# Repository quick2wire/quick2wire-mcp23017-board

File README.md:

MCP23017 Port Extender Board
============================

This repository contains the eagle files, gerbers and other material relating to the Quick2Wire MCP23017 Port Extender.
-------------------------------------------------------
Copyright (c) 2013 Quick2Wire Ltd. http://quick2wire.com

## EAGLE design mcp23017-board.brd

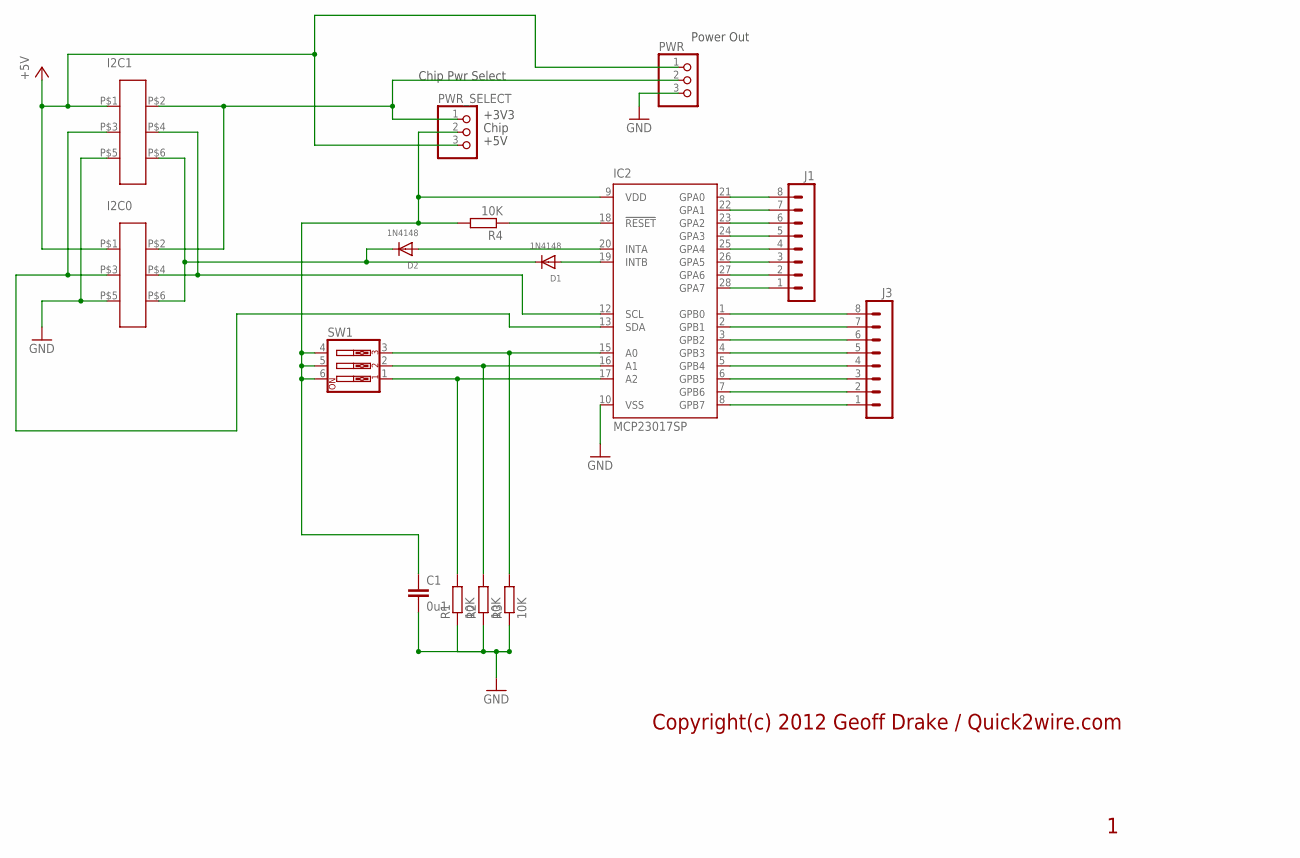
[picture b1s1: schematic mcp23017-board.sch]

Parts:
C1: 0u1; C025-030X050
D1, D2: 1N4148; DO-1N4148
I2C0, I2C1: IDC-6W
IC2: MCP23017SP; DIL28-3
J1, J3: MA08-1
PWR: PINHD-1X3; 1X03
PWR_SELECT: PINHD-1X3; 1X03
R1, R2, R3, R4: 10K; 0207/10
SW1: SW_DIP-3; EDG-03

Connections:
+3V3: I2C0.P$2, I2C1.P$2, PWR.2, PWR_SELECT.1
+5V: I2C0.P$1, I2C1.P$1, PWR.1, PWR_SELECT.3
A0: IC2.17 (A2), R1.2, SW1.1
A1: IC2.16 (A1), R2.2, SW1.2
A2: IC2.15 (A0), R3.2, SW1.3
GND: C1.2, I2C0.P$5, I2C1.P$5, IC2.10 (VSS), PWR.3, R1.1, R2.1, R3.1
unnamed: I2C0.P$3, I2C1.P$3, IC2.13 (SDA)
unnamed: I2C0.P$4, I2C1.P$4, IC2.12 (SCL)
unnamed: D1.A, IC2.19 (INTB)
unnamed: D2.A, IC2.20 (INTA)
unnamed: IC2.18 (!RESET), R4.1
unnamed: C1.1, IC2.9 (VDD), PWR_SELECT.2, R4.2, SW1.4, SW1.5, SW1.6
unnamed: D1.C, D2.C, I2C0.P$6, I2C1.P$6
PA0: IC2.21 (GPA0), J1.8
PA1: IC2.22 (GPA1), J1.7
PA2: IC2.23 (GPA2), J1.6
PA3: IC2.24 (GPA3), J1.5
PA4: IC2.25 (GPA4), J1.4
PA5: IC2.26 (GPA5), J1.3
PA6: IC2.27 (GPA6), J1.2
PA7: IC2.28 (GPA7), J1.1
PB0: IC2.1 (GPB0), J3.8
PB1: IC2.2 (GPB1), J3.7
PB2: IC2.3 (GPB2), J3.6
PB3: IC2.4 (GPB3), J3.5
PB4: IC2.5 (GPB4), J3.4
PB5: IC2.6 (GPB5), J3.3
PB6: IC2.7 (GPB6), J3.2
PB7: IC2.8 (GPB7), J3.1

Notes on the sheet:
Copyright(c) 2012 Geoff Drake / Quick2wire.com
Chip Pwr Select
+5V
+3V3
Chip
Power Out

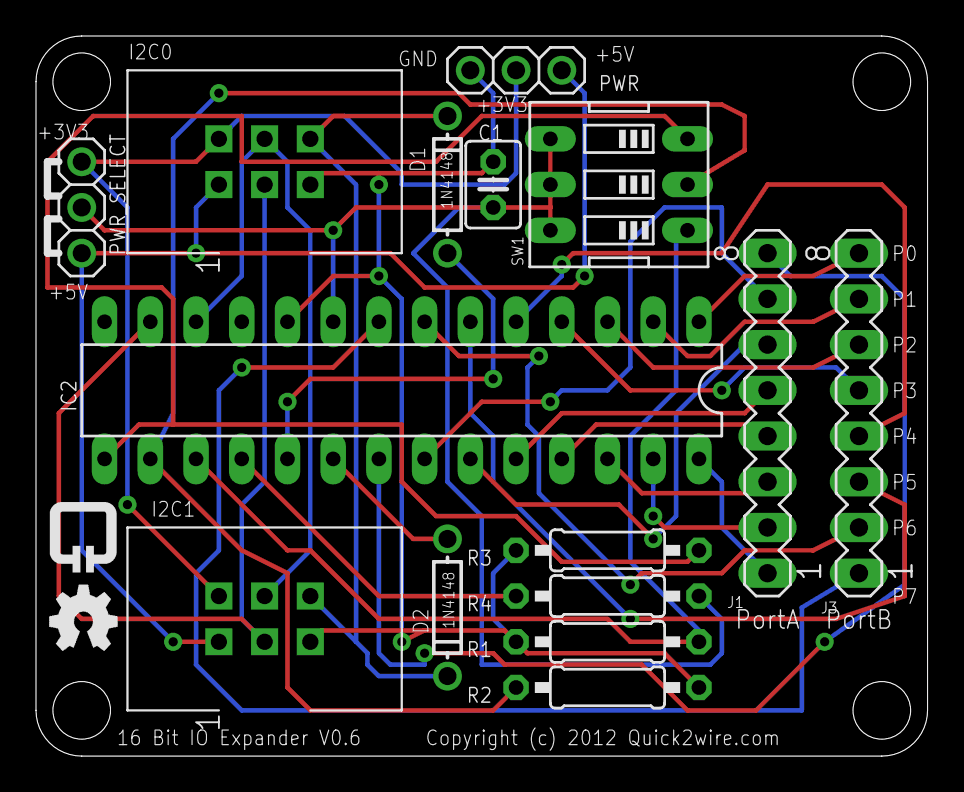
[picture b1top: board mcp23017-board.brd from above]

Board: 2 copper layers, 49.5 x 40.0 mm, 17 parts (0 on the bottom side), 29 nets.

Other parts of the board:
U$1: QUICK2WIRE-LOGO
U$2: OSHW-LOGO

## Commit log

2013-01-23 publishing version 0.5
2013-01-23 publishing version 0.6

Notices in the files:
mcp23017-board.brd:
Copyright (c) 2012 Quick2wire.com
